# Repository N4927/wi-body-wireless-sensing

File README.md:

# WI-Body

Towards an Ultra-Low-Power and High-Throughput Network for Continuous Body Monitoring

This repository contains the work developed for my Bachelor's thesis at ETH Zurich in 2025.

WI-Body investigates a wireless body-area sensing architecture designed to support continuous and energy-efficient transmission from multiple wearable sensing nodes. The project focuses on the development and experimental characterization of the wireless communication system, with particular attention to throughput, power consumption, synchronization, and multi-node operation.

## Project Overview

Wearable sensing systems for continuous body monitoring require reliable wireless communication while operating under strict energy constraints.

WI-Body explores a Wi-Fi-based architecture composed of:

- an Access Point (AP) responsible for creating and managing the wireless network;
- one or more Station nodes responsible for acquiring and transmitting sensor data;
- firmware mechanisms for communication, synchronization, and power optimization;
- a custom hardware platform designed for wearable sensing applications.

The system was developed and evaluated using ESP-IDF and ESP32-based devices.

## Key Contributions

The work carried out during the thesis includes:

- development of the Access Point and Station firmware;
- implementation and testing of TCP-based wireless communication;
- investigation of multi-node communication;
- implementation of time-synchronization mechanisms;
- evaluation of different ESP32 power-saving strategies;
- characterization of wireless throughput and power consumption;
- development and testing of a custom Wi-Body hardware platform;
- experimental analysis of the trade-off between communication performance and energy efficiency.

## Repository Structure

The repository contains the different firmware versions and experiments developed throughout the project.

Examples include:

- `SoftAP_with_tcp_server` - Access Point implementation with TCP server;
- `SoftAP_with_tcp_server_dual` - Access Point implementation for multi-node communication;
- `Station_with_tcp_client_*` - Station implementations and power-saving configurations;
- `time_synch` - time-synchronization experiments;
- `power_optimization` - power-consumption optimization experiments;
- `two_client_througput` - multi-client throughput characterization;
- `Wi-body` - hardware design files and related project material for the Wi-Body platform.

Some folders represent intermediate experimental implementations retained to document the development and characterization process.

## Development Environment

The firmware was developed using the Espressif IoT Development Framework (ESP-IDF).

### Requirements

- Visual Studio Code
- ESP-IDF extension
- ESP-IDF toolchain
- compatible ESP32 development hardware

Generated build files are intentionally excluded from the repository. When using the firmware on another computer, the corresponding ESP-IDF project may therefore need to be configured and rebuilt locally.

Before flashing any Station firmware, configure Wi-Fi credentials and host addresses locally using ESP-IDF menuconfig or the relevant configuration macros. Do not commit private SSIDs, passwords, tokens, or local machine paths.

## Hardware Setup

The Wi-Body board can be connected to a computer through UART using:

- 3.3 V
- GND
- TX
- RX

To enter flashing mode, hold the corresponding boot button while connecting the board through UART.

After flashing, reset the board to start the firmware.

## Thesis

The complete Bachelor's thesis is intended to be available in the `docs` directory:

[Alberto Fasulo - WI-Body Bachelor Thesis](docs/Alberto_Fasulo_WI-Body_Bachelor_Thesis.pdf)

Alberto Fasulo, "WI-Body: Towards an Ultra-Low-Power and High-Throughput Network for Continuous Body Monitoring", ETH Zurich, 2025.

## Author

Alberto Fasulo

Bachelor's Thesis, ETH Zurich  
2025

The project was carried out at ETH Zurich with the supervision and support of Giusy Spacone, Sebastian Frey, and Andrea Cossettini.

## Acknowledgements

I would like to thank my supervisors and the Integrated Systems Laboratory at ETH Zurich for their guidance and support throughout the project.

## License

Original software developed as part of this project is released under the [Apache License 2.0](LICENSE), unless otherwise specified.

Original documentation and figures are released under the [Creative Commons Attribution 4.0 International license](docs/LICENSE), unless otherwise specified.

Hardware design files are licensed separately under the [Solderpad Hardware License 2.1](Wi-body/LICENSE), unless otherwise specified.

Third-party software and components retain their respective original licenses.

Copyright (c) 2025 Alberto Fasulo.

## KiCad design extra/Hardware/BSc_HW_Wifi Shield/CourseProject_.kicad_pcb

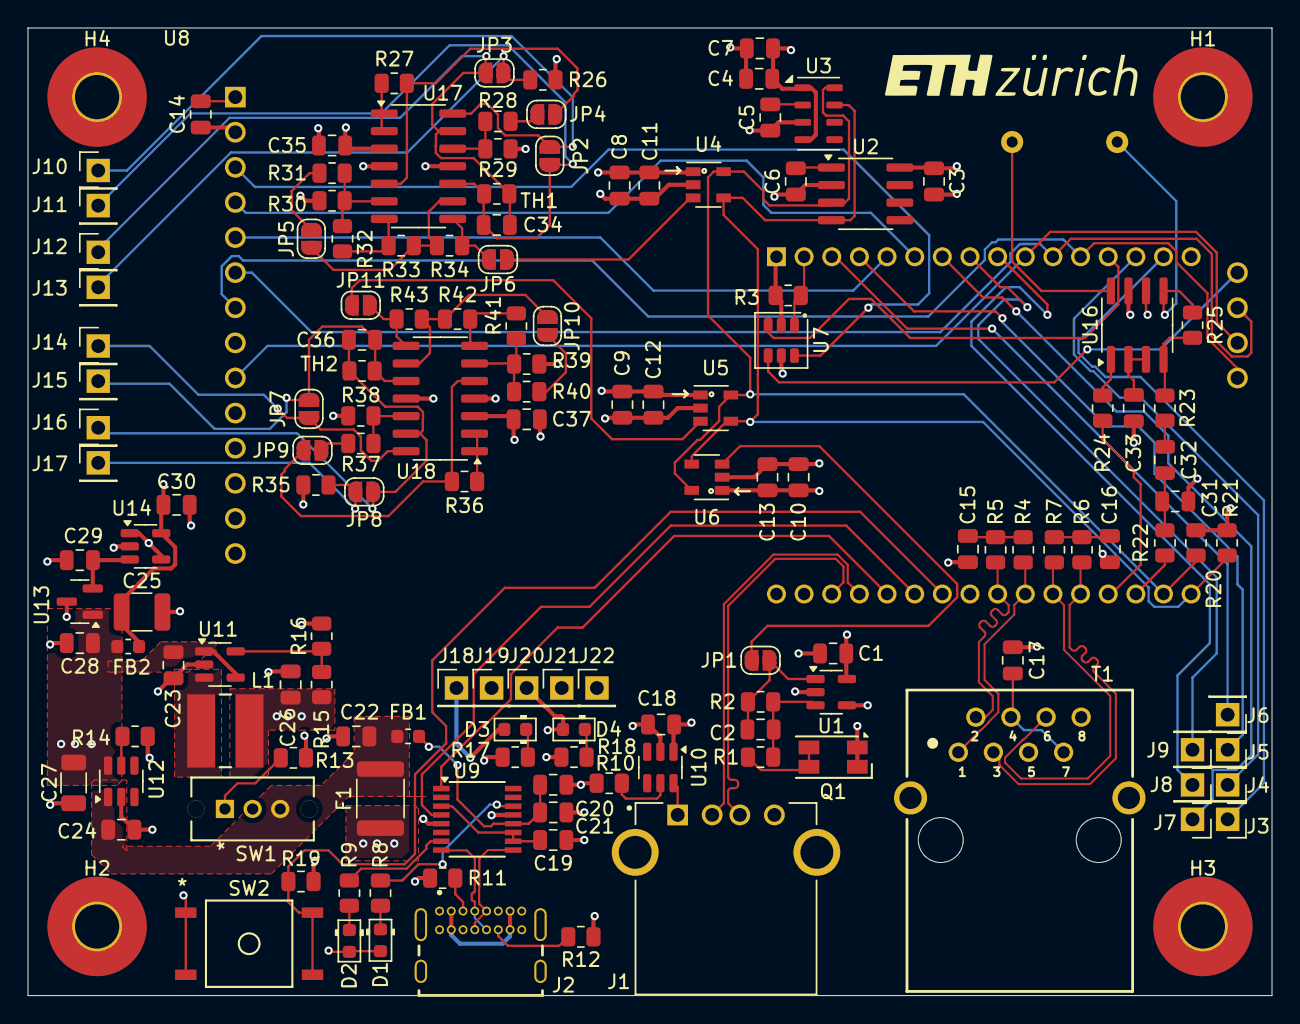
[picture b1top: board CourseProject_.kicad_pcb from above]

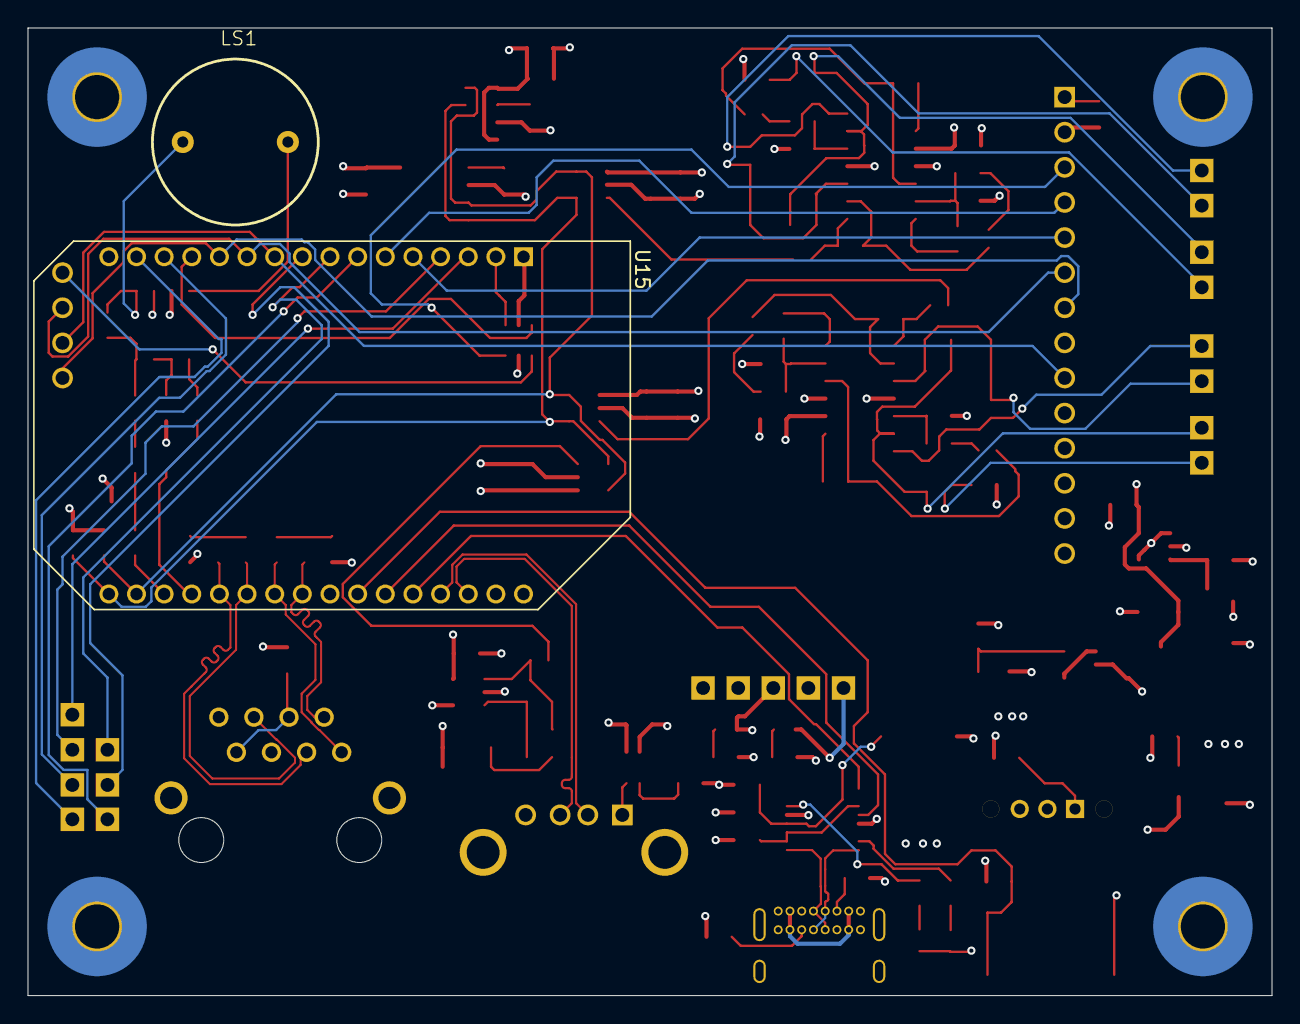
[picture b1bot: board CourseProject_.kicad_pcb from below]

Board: 4 copper layers, 90.0 x 70.0 mm, 150 parts (2 on the bottom side), 99 nets.

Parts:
C1, C2, C4, C5, C6, C11, C12, C13, C14, C15, C16, C17, C19, C20, C28, C30, C32, C33, C35, C37: 100n; C_0805_2012Metric
C3: 2.2u; C_0805_2012Metric
C7, C8, C9, C10, C24, C26: 10u; C_0805_2012Metric
C18: 1u; C_0805_2012Metric
C21, C23, C29: 4.7u; C_0805_2012Metric
C22, C34, C36: 10n; C_0805_2012Metric
C25: c=100u; C_1210_3225Metric
C27: 10uF_1206_25V; C_1206_3216Metric
C31: 47n; C_0805_2012Metric
D1, D2, D3, D4: LED; D_0603_1608Metric
F1: Polyfuse_3A_15V; Fuse_1812_4532Metric
FB1: FerriteBead - 220Ohm; L_0603_1608Metric
FB2: FerriteBead - 100Ohm; L_0603_1608Metric
H1, H2, H3, H4: MountingHole_M3_3.2mm_Pad; MountingHole_3.2mm_M3_Pad_TopBottom
J1: USB_A; UE27AC54100
J2: USB_C_Receptacle_USB2.0_16P; USB4085-GF-A
J3, J4, J5, J6, J7, J8, J9, J10, J11, J12, J13, J14, J15, J16, J17, J18, J19, J20, J21, J22: PINHD_1x1_Male; PinHeader_1x01_P2.54mm_Vertical
JP1, JP2, JP3, JP4, JP5, JP6, JP7, JP8, JP9, JP10, JP11: r=0.1; SolderJumper-2_P1.3mm_Open_RoundedPad1.0x1.5mm
L1: SRR4028-2R2Y; IND_BOURNS_SRR4028
LS1: Speaker; AL-60P06
Q1: KPS-3227; Kingbright_KPS-3227
R1: 22; R_0805_2012Metric
R2: 2k; R_0805_2012Metric
R3, R26, R27, R29, R35, R36, R38: 10k; R_0805_2012Metric
R4, R5, R6, R7: 49.9; R_0805_2012Metric
R8, R9, R17, R18: 4.7k; R_0805_2012Metric
R10: 226k; R_0805_2012Metric
R11, R12: 5.1k; R_0805_2012Metric
R13, R19, R24, R34, R43: 100k; R_0805_2012Metric
R14, R23, R25: 20k; R_0805_2012Metric
R15: 536k; R_0805_2012Metric
R16: 120k; R_0805_2012Metric
R20, R21: 3.3k; R_0805_2012Metric
R22: 1k; R_0805_2012Metric
R28, R37: 806; R_0805_2012Metric
R30, R39: 102k; R_0805_2012Metric
R31, R40: 18.7k; R_0805_2012Metric
R32, R33, R41, R42: 10.5k; R_0805_2012Metric
SW1: SS-12D07-VG 4 NS GA PA; SS12D07_CNK
SW2: FSM4JSMA
T1: 74990100011A
TH1, TH2: PT1000; R_0805_2012Metric
U1, U14: MCP6401T-xOT; SOT-23-5
U2: HIH6030-021-001; SOIC-8_3.9x4.9mm_P1.27mm
U3: MPL3115A2; NXP_LGA-8_3x5mm_P1.25mm_H1.1mm
U4: MCP3221A5T-I/OT; SOT-23-5
U5: MCP3221A7T-I/OT; SOT-23-5
U6: MCP3221A4T-I/OT; SOT-23-5
U7: 74LVC1G19; SOT-23-6
U8: Display TFT 2.4; Disp_TFT_2.4
U9: FT230XS; SSOP-16_3.9x4.9mm_P0.635mm
U10, U12: RT9728BHGE; SOT-23-6
U11: RT8097CHGB; SOT-23-5
U13: MCP1541-TT; SOT-23
U15: Omega2+; Onion_Omega2+
U16: LM4818MX/NOPB; SOIC-8_3.9x4.9mm_P1.27mm
U17, U18: MCP6404T-E-SL; SOIC-14_3.9x8.7mm_P1.27mm

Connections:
0: C1.2 (-), C3.2 (-), C4.1 (+), C5.1 (+), C6.1 (+), C7.2 (-), C8.2 (-), C9.2 (-), C10.2 (-), C11.1 (+), C12.1 (+), C13.1 (+), C14.1 (+), C15.1 (+), C16.1 (+), C17.1 (+), C18.2 (-), C19.1 (+), C20.1 (+), C21.2 (-), C22.2 (-), C23.2 (-), C24.2 (-), C25.2, C26.2 (-), C27.2, C28.2 (-), C29.2 (-), C30.2 (-), C31.2 (-), C33.2 (-), C35.1 (+), C37.1 (+), J1.4 (GND), J1.5 (Shield), J2.A1 (GND), J2.A12 (GND), J2.B1 (GND), J2.B12 (GND), J2.S1 (SHIELD), J22.1, R3.2 (-), R10.1 (+), R11.1 (+), R12.1 (+), R13.2 (-), R14.2 (-), R16.2 (-), R17.2 (-), R18.2 (-), R19.2 (-), R26.2 (-), R29.2 (-), R30.1 (+), R35.2 (-), R38.2 (-), R39.1 (+), T1.0, U1.2 (V-), U2.2 (VSS), U3.3 (GND), U4.2 (GND), U5.2 (GND), U6.2 (GND), U7.2 (GND), U8.2 (GND), U9.5 (GND), U9.13 (GND), U10.2 (GND), U11.2 (GND), U12.2 (GND), U13.3 (Vss), U14.2 (V-), U15.1 (GND), U15.32 (GND), U16.7 (GND), U17.11 (V-), U18.11 (V-)
3.3V: C3.1 (+), C4.2 (-), C7.1 (+), C14.2 (-), C26.1 (+), D1.2 (A), D2.2 (A), D3.2 (A), J18.1, L1.2, R15.1 (+), R20.1 (+), R21.1 (+), SW2.1, SW2.2, U2.8 (VDD), U3.1 (VDD), U3.4 (VDDIO), U7.5 (VCC), U8.1 (VCC), U8.8 (LED), U15.31 (3.3V_VIN), U16.6 (VDD)
5V: C18.1 (+), C23.1 (+), C27.1, C28.1 (+), D4.2 (A), FB2.1, J20.1, U10.1 (VIN), U11.1 (EN), U11.4 (VIN), U12.6 (VOUT), U13.1 (Vin)
+4.096V: C8.1 (+), C9.1 (+), C10.1 (+), C11.2 (-), C12.2 (-), C13.2 (-), C35.2 (-), C37.2 (-), J21.1, U1.4 (-), U4.1 (VDD), U5.1 (VDD), U6.1 (VDD), U14.1, U14.4 (-), U17.3 (+), U18.3 (+)
/A_TEMP1: JP6.1 (A), U4.3 (AIN)
/A_TEMP2: JP11.1 (A), U5.3 (AIN)
/Audio/SPEAKER: R22.2 (-), U15.19
/Audio/nSPEAKER_EN: R24.2 (-), U15.20 (18)
/Display/DISP_D/C: U8.5 (D/~C), U15.5 (17)
/Display/DISP_SPI.MISO: U8.9 (MISO), U8.17 (SD_MISO), U15.10 (9/SPI_MISO)
/Display/DISP_SPI.MOSI: U8.6 (MOSI), U8.16 (SD_MOSI), U15.11 (8/SPI_MOSI)
/Display/DISP_SPI.SCLK: U8.7 (SCK), U8.18 (SD_SCK), U15.12 (7/SPI_CLK)
/Display/DISP_SPI.SS: U7.3 (~E), U15.13 (6/SPI_CS1)
/Display/RST_DISP: U8.4 (RESET), U15.6 (16)
/Display/TFT/SD: R3.1 (+), U7.1 (A), U15.2 (11)
/Ethernet/ENET_RX_N: R7.2 (-), T1.6 (RD-), U15.22 (ETH_RX-)
/Ethernet/ENET_RX_P: R6.2 (-), T1.3 (RD+), U15.21 (ETH_RX+)
/Ethernet/ENET_TX_N: R5.2 (-), T1.2 (TD-), U15.24 (ETH_TX-)
/Ethernet/ENET_TX_P: R4.2 (-), T1.1 (TD+), U15.23 (ETH_TX+)
/Light Detector/A_LIGHT: JP1.1 (A), U6.3 (AIN)
/Omega2+/GPIO_0: J3.1, U15.15 (0/I2S_SDI)
/Omega2+/GPIO_1: J4.1, U15.14 (1/I2S_SDO)
/Omega2+/GPIO_2: J5.1, U15.4 (2/I2S_WS)
/Omega2+/GPIO_3: J6.1, U15.3 (3/I2S_CLK)
/Omega2+/GPIO_15: J7.1, U15.7 (15)
/Omega2+/GPIO_45: J8.1, U15.9 (SER1_TX/45)
/Omega2+/GPIO_46: J9.1, U15.8 (SER1_RX/46)
/Omega2+/I2C.SCL: R20.2 (-), U2.3 (SCL), U3.8 (SCL), U4.5 (SCL), U5.5 (SCL), U6.5 (SCL), U15.18 (I2C_SCL/4)
/Omega2+/I2C.SDA: R21.2 (-), U2.4 (SDA), U3.7 (SDL), U4.4 (SDA), U5.4 (SDA), U6.4 (SDA), U15.17 (I2C_SDA/5)
/Omega2+/RESET: R19.1 (+), SW2.3, SW2.4, U15.26 (FW_RST/38)
/USBs/UART_RX: U9.4 (RXD), U15.27 (SER0_TX/12)
/USBs/UART_TX: U9.1 (TXD), U15.28 (SER0_RX/13)
/USBs/USBHOST_N: J1.2 (D-), U15.29 (USB_D-)
/USBs/USBHOST_P: J1.3 (D+), U15.30 (USB_D+)
/USBs/USB_N: J2.A7 (D-), J2.B7 (D-), U9.9 (USBDM)
/USBs/USB_P: J2.A6 (D+), J2.B6 (D+), U9.8 (USBDP)
unnamed: C2.1 (+), JP1.2 (B), R2.1 (+), U1.1
unnamed: C2.2 (-), R1.2 (-), R2.2 (-), U1.3 (+)
unnamed: C5.2 (-), U3.2 (CAP)
unnamed: C6.2 (-), U2.1 (VCORE)
unnamed: C15.2 (-), R4.1 (+), R5.1 (+)
unnamed: C16.2 (-), R6.1 (+), R7.1 (+)
unnamed: C17.2 (-), T1.4 (TCT), T1.7 (RCT)
unnamed: C19.2 (-), U9.3 (VCCIO), U9.10 (3V3OUT), U9.11 (~RESET)
unnamed: C20.2 (-), C21.1 (+), FB1.1, U9.12 (VCC)
unnamed: C29.1 (+), U13.2 (Vout), U14.3 (+)
unnamed: C31.1 (+), C32.1 (+), R22.1 (+)
unnamed: C32.2 (-), R23.2 (-)
unnamed: C33.1 (+), U16.2 (BYPASS), U16.3 (+IN)
unnamed: C34.1 (+), J11.1, JP2.1 (A), TH1.1, U17.10 (+)
unnamed: C34.2 (-), J12.1, JP3.2 (B), TH1.2, U17.13 (-)
unnamed: C36.1 (+), J15.1, JP7.1 (A), TH2.1, U18.10 (+)
unnamed: C36.2 (-), J16.1, JP8.2 (B), TH2.2, U18.13 (-)
unnamed: D1.1 (K), R8.1 (+)
unnamed: D2.1 (K), R9.1 (+)
unnamed: D3.1 (K), R17.1 (+)
unnamed: D4.1 (K), R18.1 (+)
unnamed: F1.1, J2.A4 (VBUS), J2.A9 (VBUS), J2.B4 (VBUS), J2.B9 (VBUS)
unnamed: J1.1 (VBUS), U10.6 (VOUT)
unnamed: J2.A5 (CC1), R11.2 (-)
unnamed: J2.B5 (CC2), R12.2 (-)
unnamed: J10.1, JP2.2 (B), U17.14
unnamed: J13.1, JP3.1 (A), R26.1 (+)
unnamed: JP4.1 (A), R28.2 (-)
unnamed: JP4.2 (B), R27.1 (+), U17.5 (+)
unnamed: JP5.1 (A), R33.2 (-), R34.1 (+), U17.9 (-)
unnamed: JP5.2 (B), R31.2 (-)
unnamed: JP6.2 (B), R34.2 (-), U17.8
unnamed: J14.1, JP7.2 (B), U18.14
unnamed: J17.1, JP8.1 (A), R35.1 (+)
unnamed: JP9.1 (A), R37.2 (-)
unnamed: JP9.2 (B), R36.1 (+), U18.5 (+)
unnamed: JP10.1 (A), R42.2 (-), R43.1 (+), U18.9 (-)
unnamed: JP10.2 (B), R40.2 (-)
unnamed: JP11.2 (B), R43.2 (-), U18.8
unnamed: Q1.2, Q1.4, R1.1 (+)
unnamed: R8.2 (-), U9.14 (CBUS1)
unnamed: R9.2 (-), U9.7 (CBUS2)
unnamed: R10.2 (-), U10.5 (ILIM)
unnamed: R13.1 (+), SW1.1
unnamed: R14.1 (+), U12.5 (ILIM)
unnamed: R15.2 (-), R16.1 (+), U11.5 (FB)
unnamed: R23.1 (+), R25.2 (-), U16.4 (-IN)
unnamed: R24.1 (+), U16.1 (SD)
unnamed: LS1.1, R25.1 (+), U16.5 (VOUT1)
unnamed: R27.2 (-), U17.1, U17.2 (-)
unnamed: R28.1 (+), R29.1 (+), U17.12 (+)
unnamed: R30.2 (-), R31.1 (+), R32.1 (+), U17.6 (-)
unnamed: R32.2 (-), R33.1 (+), U17.7
unnamed: R36.2 (-), U18.1, U18.2 (-)
unnamed: R37.1 (+), R38.1 (+), U18.12 (+)
unnamed: R39.2 (-), R40.1 (+), R41.1 (+), U18.6 (-)
unnamed: R41.2 (-), R42.1 (+), U18.7
unnamed: U7.6 (Y0), U8.3 (~CS)
unnamed: U7.4 (Y1), U8.15 (SD_CS)
unnamed: L1.1, U11.3 (SW)
unnamed: LS1.2, U16.8 (VOUT2)
VBUS: C22.1 (+), C24.1 (+), F1.2, FB1.2, SW1.3, U12.1 (VIN)
VDDA: C1.1 (+), C25.1, C30.1 (+), FB2.2, J19.1, Q1.1, Q1.3, U1.5 (V+), U14.5 (V+), U17.4 (V+), U18.4 (V+)

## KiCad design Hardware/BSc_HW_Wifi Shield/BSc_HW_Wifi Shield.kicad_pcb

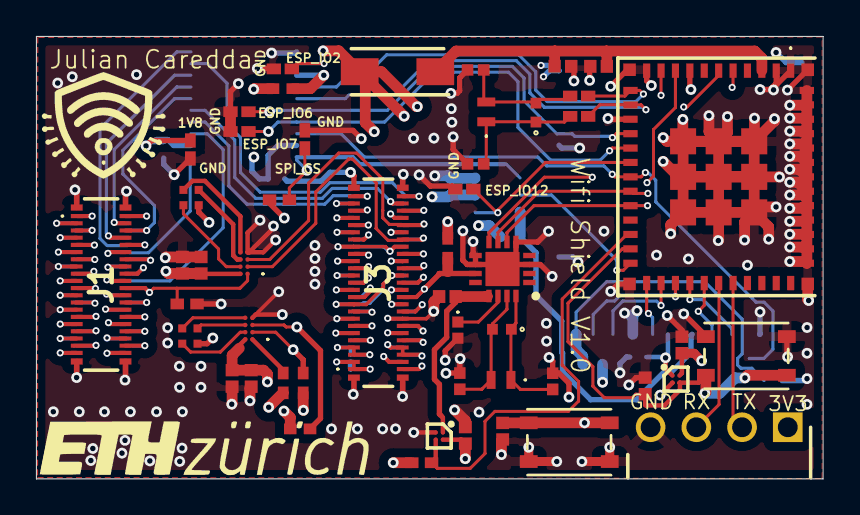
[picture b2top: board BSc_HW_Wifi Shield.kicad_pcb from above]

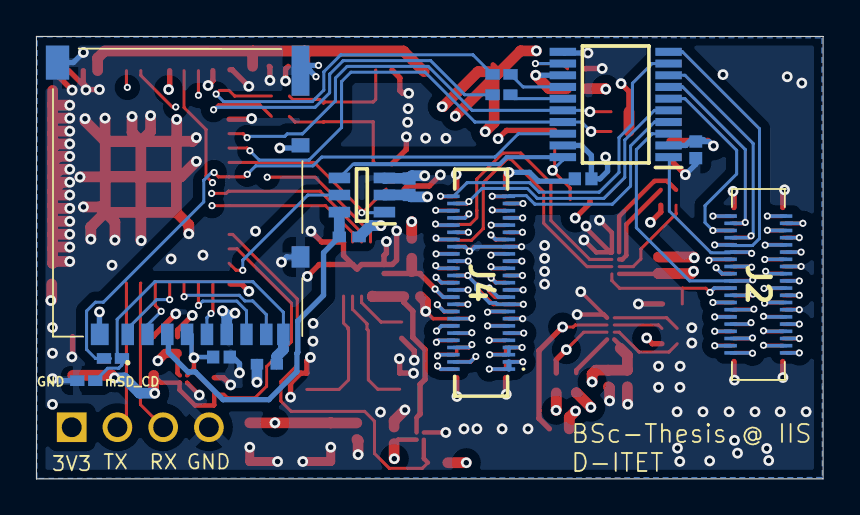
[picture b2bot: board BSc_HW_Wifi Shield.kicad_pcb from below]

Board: 6 copper layers, 43.7 x 24.6 mm, 65 parts (15 on the bottom side), 118 nets.

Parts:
C1, C2, C5, C11, C16, C19, C20: 0.1 uF; CAPC1005X55N
C3, C8, C9, C10, C15, C17, C18: 1 uF; CAPC1005X55N
C4: 22 uF; CAPC1005X75N
C6, C7, C12, C13: 12 pF; CAPC1005X56N
C14: 47pF; CBR04C160F5GAC
D1: SS14; DIOM5126X250N
IC1: TXB0108PWR; SOP65P640X120-20N
IC2: TMUX1219DBVRQ1; SOT95P280X145-6N
IC3: ESP32-C6-MINI-1-H8; ESP32C6MINI1H8
IC4, IC6: Power Switch; BGA4C40P2X2_78X78X50
IC5: AM1805AQ; QFN50P300X300X90-17N
IC7, IC8: IS31FL3194-CLS2-TR; IS31FL3194CLS2TR
J1: DF40C-40DP-0.4V_51_; DF40C40DP04V51
J2: DF40HC_3.0_-40DS-0.4V_51_; DF40HC3040DS04V51
J3: DF40C-50DP-0.4V_51_; DF40C50DP04V51
J4: DF40HC_3.0_-50DS-0.4V_51_; DF40HC3050DS04V51
J5: HTSW-104-08-G-S-RA; HDRRA4W64P0X254_1X4_1016X254X309P
J6: DM3AT-SF-PEJM5_40_; DM3ATSFPEJM540
LED1, LED2: SML-LX0404SIUPGUSB
R1, R3, R4, R6, R7, R8, R9, R10, R11, R12, R15, R16: 0; RESC1005X35N
R2, R5, R17, R23: 100 k; RESC1005X45N
R13, R19, R20, R21, R22, R24: 4.7 k; RESC1005X37N
R14, R18: 10 M; RCC0402_e3
SW1, SW2: PTS815 SJM 250 SMTR LFS; SW4_PTS815 SJM 250 SMTR LFS_CNK
Y1, Y2: ABS05W-32.768KHZ-D-2-T; ABS05W32768KHZD2T

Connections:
1V8: C1.1, IC1.2 (VCCA), J3.11, J3.13, J4.11, J4.13, R1.1
+3.3V: C2.1, C3.1, C10.2, C15.2, C17.1, C18.1, C19.1, C20.1, D1.2 (A), IC1.19 (VCCB), IC2.2 (VDD), IC4.A2 (VIN), IC6.A2 (VIN), IC7.A2 (VCC), IC8.A2 (VCC), J3.19, J3.28, J4.19, J4.28, J5.1, LED1.1 (COMMON_ANODE), LED2.1 (COMMON_ANODE), R2.1, R5.1, R13.2, R17.1, R19.1, R20.1, R21.1, R22.1, R24.1
/ADS_A_DR: J3.43, J4.43
/ADS_B_DR: J3.45, J4.45
/CSI_CLK_N: J1.17, J2.17
/CSI_CLK_P: J1.19, J2.19
/CSI_D0_N: J1.23, J2.23
/CSI_D0_P: J1.25, J2.25
/Conn_24: J1.24, J2.24
/Conn_28: J1.28, J2.28
/Conn_30: J1.30, J2.30
/Conn_32: J1.32, J2.32
/ESP/ESP_EN: C9.1, IC1.13 (B7), IC3.8 (EN), R13.1, SW2.1, SW2.2
/ESP/ESP_IO0: IC3.12 (IO0), R11.2, R16.2
/ESP/ESP_IO1: IC3.13 (IO1), R12.2, R15.2
/ESP/ESP_IO2: IC1.12 (B8), IC3.5 (IO2), R7.1
/ESP/ESP_IO3: IC3.6 (IO3), IC5.8 (CLKOUT/NIRQ3)
/ESP/ESP_IO8: IC3.22 (IO8), IC4.B2 (ON), R17.2
/ESP/ESP_IO12: IC2.1 (SEL), IC3.17 (IO12), R6.1
/ESP/ESP_IO13: IC1.18 (B2), IC3.18 (IO13), R3.2
/ESP/ESP_IO14: IC3.19 (IO14), IC5.7 (SCL), IC7.C1 (SCL), R24.2
/ESP/ESP_IO15: IC3.20 (IO15), IC5.6 (SDA), IC7.B1 (SDA), R22.2
/ESP/ESP_IO18: IC2.5 (D), IC3.24 (IO18)
/ESP/ESP_RXDO: IC3.30 (RXD0), J5.3
/ESP/ESP_TXDO: IC3.31 (TXD0), J5.2
/ESP/LEDs/ESP_LED_Driver_SDB: IC7.A1 (SDB), R21.2
/ESP/SPI_ESP_CS_MUX: IC1.20 (B1), IC2.4 (S1), R2.2, R10.1
/ESP/nRF_P1.00_GAP_GPIO60_ESP_IO00: IC1.14 (B6), R11.1
/ESP/nRF_P1.00_GAP_GPIO61_ESP_IO01: IC1.15 (B5), R12.1
/EXT_CHG/VUSB: J3.6, J3.8, J4.6, J4.8
/GAP_GPIO46: J1.29, J2.29
/GAP_GPIO47: J1.31, J2.31
/GAP_GPIO48: J1.37, J2.37
/GAP_GPIO49: J1.39, J2.39
/GAP_GPIO50: J1.33, J2.33
/GAP_GPIO51: J1.35, J2.35
/I2C_A_SCL: J3.30, J4.30
/I2C_A_SDA: J3.32, J4.32
/JTAG_GAP9_RESET_N: J1.1, J2.1
/JTAG_GAP9_TCK: J1.5, J2.5
/JTAG_GAP9_TDI: J1.9, J2.9
/JTAG_GAP9_TDO: J1.11, J2.11
/JTAG_GAP9_TMS/CS_RAM_GATE: J1.7, J2.7
/JTAG_GAP9_VCC: J1.13, J2.13
/JTAG_GAP9_~TRST: J1.3, J2.3
/MIC_CLK: J1.36, J2.36
/MIC_DATA: J1.34, J2.34
/MIC_THSEL: J1.38, J2.38
/MIC_WAKE: J1.40, J2.40
/MSP_CS: J3.23, J4.23
/MSP_DR1: J3.25, J4.25
/MSP_DR2: J3.41, J4.41
/MSP_TCK: IC1.16 (B4), IC3.15 (IO6), J3.4, J4.4, R8.1
/MSP_TDI: IC3.10 (IO5), J3.24, J4.24
/MSP_TDO: IC1.17 (B3), IC3.16 (IO7), J3.26, J4.26, R9.1
/MSP_TMS: IC3.9 (IO4), IC5.11 (FOUT/NIRQ), J3.22, J4.22, R19.2
/MSP_~TRST: J3.2, J4.2
/QVR_IMU_1: J1.16, J2.16
/QVR_IMU_2: J1.18, J2.18
/SPI_A_CLK: J3.40, J4.40
/SPI_A_CS: J3.46, J4.46
/SPI_A_MISO: J3.34, J4.34
/SPI_A_MOSI: J3.44, J4.44
/SPI_B_CLK: IC1.5 (A4), J3.48, J4.48
/SPI_B_CS: J3.47, J4.47
/SPI_B_MISO: IC1.9 (A8), J3.50, J4.50
/SPI_B_MOSI: IC1.4 (A3), J3.49, J4.49
/SWDCLK: J3.12, J4.12
/SWDIO: J3.10, J4.10
/SWO: J3.14, J4.14
/VQPS_FUSE_1V8: J1.14, J2.14
/nRF_P0.04: IC1.3 (A2), J1.20, J2.20
/nRF_P0.07/AMUX: J1.26, J2.26
/nRF_P0.12_GAP_GPIO64: IC1.1 (A1), J1.12, J2.12
/nRF_P0.31: J1.2, J2.2
/nRF_P1.00_GAP_GPIO60: IC1.7 (A6), J1.4, J2.4
/nRF_P1.01_GAP_GPIO61: IC1.6 (A5), J1.6, J2.6
/nRF_P1.09_GAP_GPIO62: IC1.8 (A7), J1.8, J2.8
/nRF_P1.11_GAP_GPIO63: IC1.10 (OE), J1.10, J2.10
/nRF_QSPI_CLK: J3.39, J4.39
/nRF_QSPI_CS_CONN: J3.27, J4.27
/nRF_QSPI_IO0: J3.37, J4.37
/nRF_QSPI_IO1: J3.33, J4.33
/nRF_QSPI_IO2: J3.31, J4.31
/nRF_QSPI_IO3: J3.29, J4.29
/~RST: J3.9, J4.9
GND: C1.2, C2.2, C3.2, C4.2, C5.2, C6.1, C7.2, C8.2, C9.2, C10.1, C11.2, C12.1, C13.2, C14.2, C15.1, C16.2, C17.2, C18.2, C19.2, C20.2, IC1.11 (GND), IC2.3 (GND), IC3.1 (GND_1), IC3.2 (GND_2), IC3.11 (GND_3), IC3.14 (GND_4), IC3.36 (GND_5), IC3.37 (GND_6), IC3.38 (GND_7), IC3.39 (GND_8), IC3.40 (GND_9), IC3.41 (GND_10), IC3.42 (GND_11), IC3.43 (GND_12), IC3.44 (GND_13), IC3.45 (GND_14), IC3.46 (GND_15), IC3.47 (GND_16), IC3.48 (GND_17), IC3.49 (GND_18), IC3.50 (GND_19), IC3.51 (GND_20), IC3.52 (GND_21), IC3.53 (GND_22), IC3.54 (GND_23), IC3.55 (GND_24), IC3.56 (GND_25), IC3.57 (GND_26), IC3.58 (GND_27), IC3.59 (GND_28), IC3.60 (GND_29), IC3.61 (GND_30), IC4.B1 (GND), IC5.3 (NEXTR), IC5.5 (VBAT), IC5.9 (VSS_1), IC5.10 (EXTI), IC5.17 (VSS_2), IC6.B1 (GND), IC7.D1 (GND), IC8.D1 (GND), J1.15, J1.21, J1.27, J1.MP1, J1.MP2, J1.MP3, J1.MP4, J2.15, J2.21, J2.27, J3.15, J3.16, J3.35, J3.36, J3.51 (MP1), J3.52 (MP2), J3.53 (MP3), J3.54 (MP4), J4.15, J4.16, J4.35, J4.36, J5.4, J6.6 (VSS), J6.MP1, J6.MP2, J6.MP3, J6.MP4, J6.MP5, R1.2, R4.2, R6.2, R7.2, R8.2, R9.2, R10.2, R23.2, SW1.3, SW1.4, SW2.3, SW2.4
unnamed: C6.2, R14.1, R15.1, Y1.1
unnamed: C7.1, R14.2, R16.1, Y1.2
unnamed: C4.1, C5.1, D1.1 (K), IC3.3 (3V3)
unnamed: C11.1, IC4.A1 (VOUT), IC5.13 (VCC)
unnamed: C14.1, IC5.14 (AF)
unnamed: C12.2, IC5.16 (XI), R18.1, Y2.1
unnamed: C13.1, IC5.15 (XO), R18.2, Y2.2
unnamed: C16.1, IC6.A1 (VOUT), J6.4 (VDD)
unnamed: IC7.B2 (OUT1), LED1.2 (CATHODE_RED)
unnamed: IC7.C2 (OUT2), LED1.4 (CATHODE_GREEN)
unnamed: IC7.D2 (OUT3), LED1.3 (CATHODE_BLUE)
unnamed: IC8.B2 (OUT1), LED2.2 (CATHODE_RED)
unnamed: IC8.C2 (OUT2), LED2.4 (CATHODE_GREEN)
unnamed: IC8.D2 (OUT3), LED2.3 (CATHODE_BLUE)
Nordiq_LED_SCL: IC8.C1 (SCL), J3.42, J4.42
Nordiq_LED_SDA: IC8.B1 (SDA), J3.38, J4.38
Nordiq_LED_SDB: IC8.A1 (SDB), J1.22, J2.22, R23.1
VA0: J3.20, J4.20
VA1: J3.21, J4.21
VD0: J3.18, J4.18
VD1: J3.17, J4.17
Vbat: J3.1, J3.3, J4.1, J4.3
Vsys: J3.5, J3.7, J4.5, J4.7
mSD_CD: J6.CD1 (CARD_DETECT), R3.1, R4.1, R20.2
mSD_CLK: IC3.25 (IO19), J6.5 (CLK)
mSD_CMD: IC2.6 (S2), J6.3 (CMD), R5.2
mSD_DAT0: IC3.26 (IO20), J6.7 (DAT0)
mSD_DAT1: IC3.27 (IO21), J6.8 (DAT1)
mSD_DAT2: IC3.28 (IO22), J6.1 (DAT2)
mSD_DAT3: IC3.29 (IO23), J6.2 (CD/DAT3)
microSD_ON/OFF: C8.1, IC3.23 (IO9), IC6.B2 (ON), SW1.1, SW1.2

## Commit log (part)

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2024-10-21 add gitignore
2024-10-22 add Blinky
2024-10-31 add tcp_client
2024-10-31 add iPerf
2024-10-31 test project import
2024-11-01 modified gitignore
2024-11-01 tcp_client
2024-11-01 latest working version
2024-11-19 testing
2024-11-20 updating_AP
2024-11-20 Adding_STA
2024-12-09 Add PCB template
2025-01-24 Uploading Firmware in its final state and Hardware design files as used for printing PCBs
2025-01-24 Experiment Data and Theory files
2025-01-27 README added, contains info on Firmware and Hardware
2025-06-18 final code
2025-07-29 added experimental result
2025-07-29 Upload New File
2025-07-29 added result
2025-07-29 Result added
